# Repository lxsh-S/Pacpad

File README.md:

# Pacpad

*Pacpad* is a 4-key macropad with a rotatory encoder, an OLED screen and 2LEDs !!!!!!

I've used the KMK firmware for this macropad as python is way more easier than C.

## firmware fucntions

- Media control(prev track, play/pause, next track) with the SW2, SW3, and SW4 keys respectively
- Volume control with the rotatory encoder(volume up, volume down and mute)
- The SW1 key is binded with the F11 key for fullscreen

## PCB

This is my first ever PCB that I made in Kicad. I changed the design like 4 times lol T_T

PCB:

Schematic:

3D:

## CAD

This case was made in fusion360(I dualbooted win11 for that :))

- Top:

- Bottom: `Note` -> `The hole at the bottom of this design is for a screw that I already have with me (It is to hold the PCB at one place)`

- Knob: `Used the same as orpheuspad pad`

- Assembled:

## BOM

- 4x MX-Style switches
- 4x Black DSA Keys  
- 1x EC11 Rotatory encoder
- 1x 0.91 inch OLED display
- 2x SK6812MINI-E LEDs
- 1x Seed Xiao RP2040
- PCB made from the gerbers in the repo
- The top, bottom cases with the volume knob to be 3d printed from the `Production` folder

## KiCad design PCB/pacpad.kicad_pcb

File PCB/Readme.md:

# PCB

This pcb and the schematics were made in Kicad(it was my first time using it!)

## Design

- I first went through the default design that the hackpad kit's tutorial shows us
- Then I built on top of it and added another key, LEDs, OLED display and also a rotatory encoder
- I had to reroute the pcb way too many times cuz I was bring in major changes with each design change
- I didnt use matrix for the keys because we are only using 4 keys and ill be using up 4 GPIO pins anyway in the matrix

## Mistakes and Learnings

- The footprints and symbols are the most important thing for designing pcbs!! - I forgot this way too many times :(
- Learnt to use Kicad and also how footprints work and how really does a pcb work, it;s just a normal connection that we can build with a breadboard (but way more harder). Custom printed boards are used so that we can minimize the mess that we'll create traditionally!

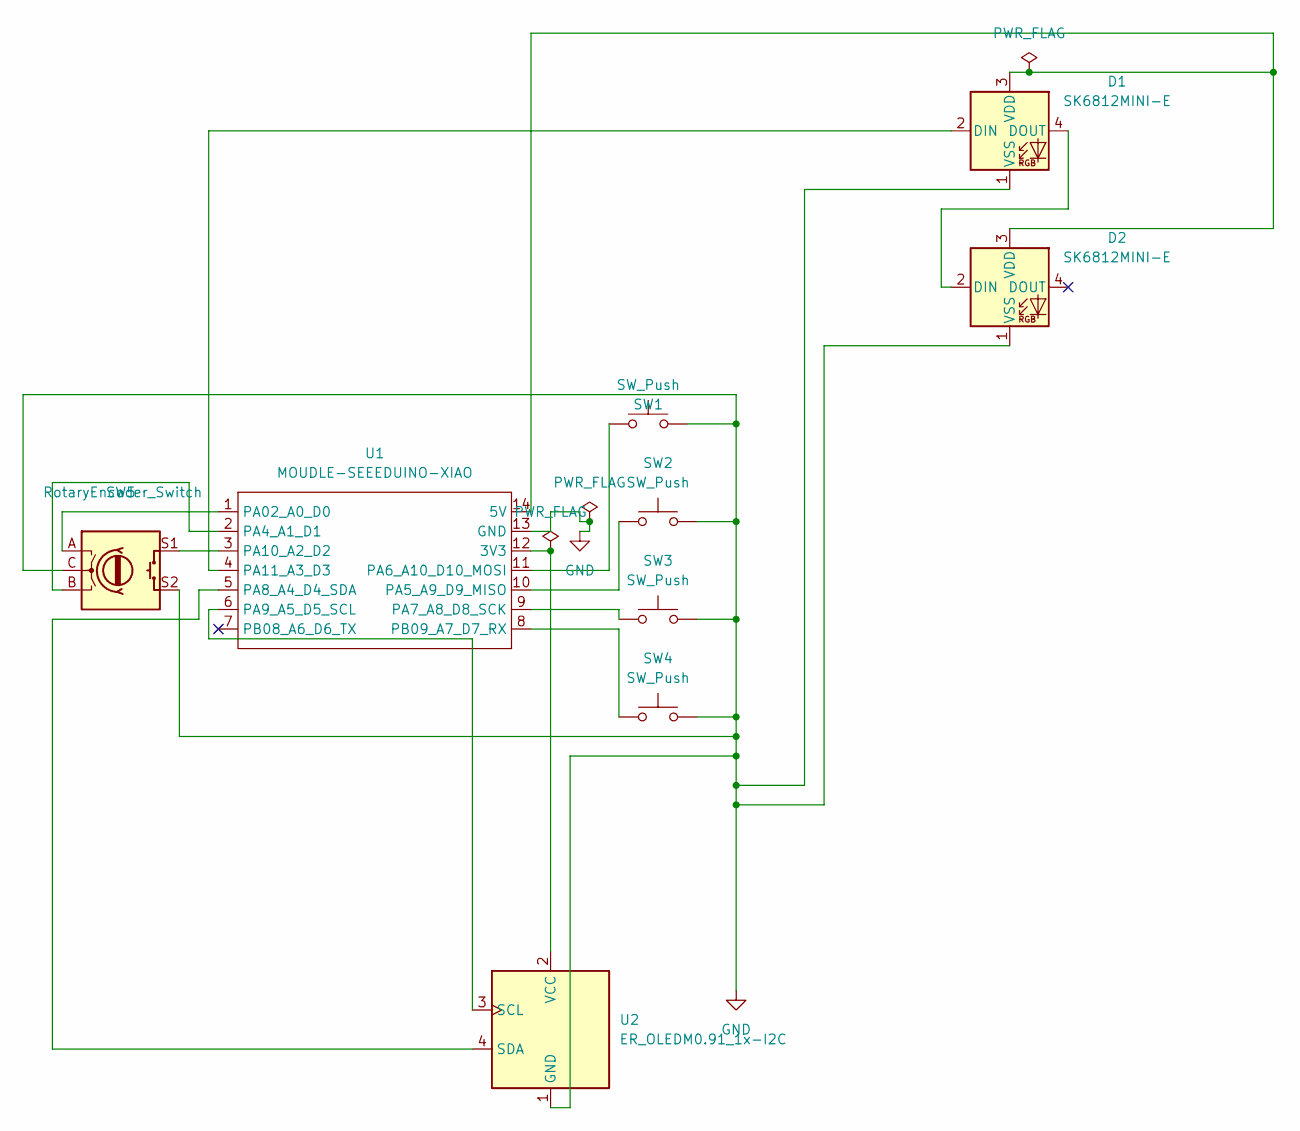
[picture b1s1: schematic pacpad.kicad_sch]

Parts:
D1, D2: SK6812MINI-E; SK6812MINI-E_fixed
SW1, SW2, SW3, SW4: SW_Push; SW_Cherry_MX_1.00u_PCB
SW5: RotaryEncoder_Switch; RotaryEncoder_Alps_EC11E-Switch_Vertical_H20mm_CircularMoun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
U1: MOUDLE-SEEEDUINO-XIAO; XIAO-Generic-Hybrid-14P-2.54-21X17.8MM
U2: ER_OLEDM0.91_1x-I2C

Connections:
GND: D1.1 (VSS), D2.1 (VSS), SW1.2, SW2.2, SW3.2, SW4.2, SW5.C, SW5.S2, U1.13 (GND), U2.1 (GND)
unnamed: D1.2 (DIN), U1.4 (PA11_A3_D3)
unnamed: D1.4 (DOUT), D2.2 (DIN)
unnamed: D1.3 (VDD), D2.3 (VDD), U1.14 (5V)
unnamed: U1.12 (3V3), U2.2 (VCC)
unnamed: SW5.A, U1.1 (PA02_A0_D0)
unnamed: SW5.B, U1.2 (PA4_A1_D1)
unnamed: SW2.1, U1.10 (PA5_A9_D9_MISO)
unnamed: SW1.1, U1.11 (PA6_A10_D10_MOSI)
unnamed: SW3.1, U1.9 (PA7_A8_D8_SCK)
unnamed: U1.5 (PA8_A4_D4_SDA), U2.4 (SDA)
unnamed: U1.6 (PA9_A5_D5_SCL), U2.3 (SCL)
unnamed: SW5.S1, U1.3 (PA10_A2_D2)
unnamed: SW4.1, U1.8 (PB09_A7_D7_RX)

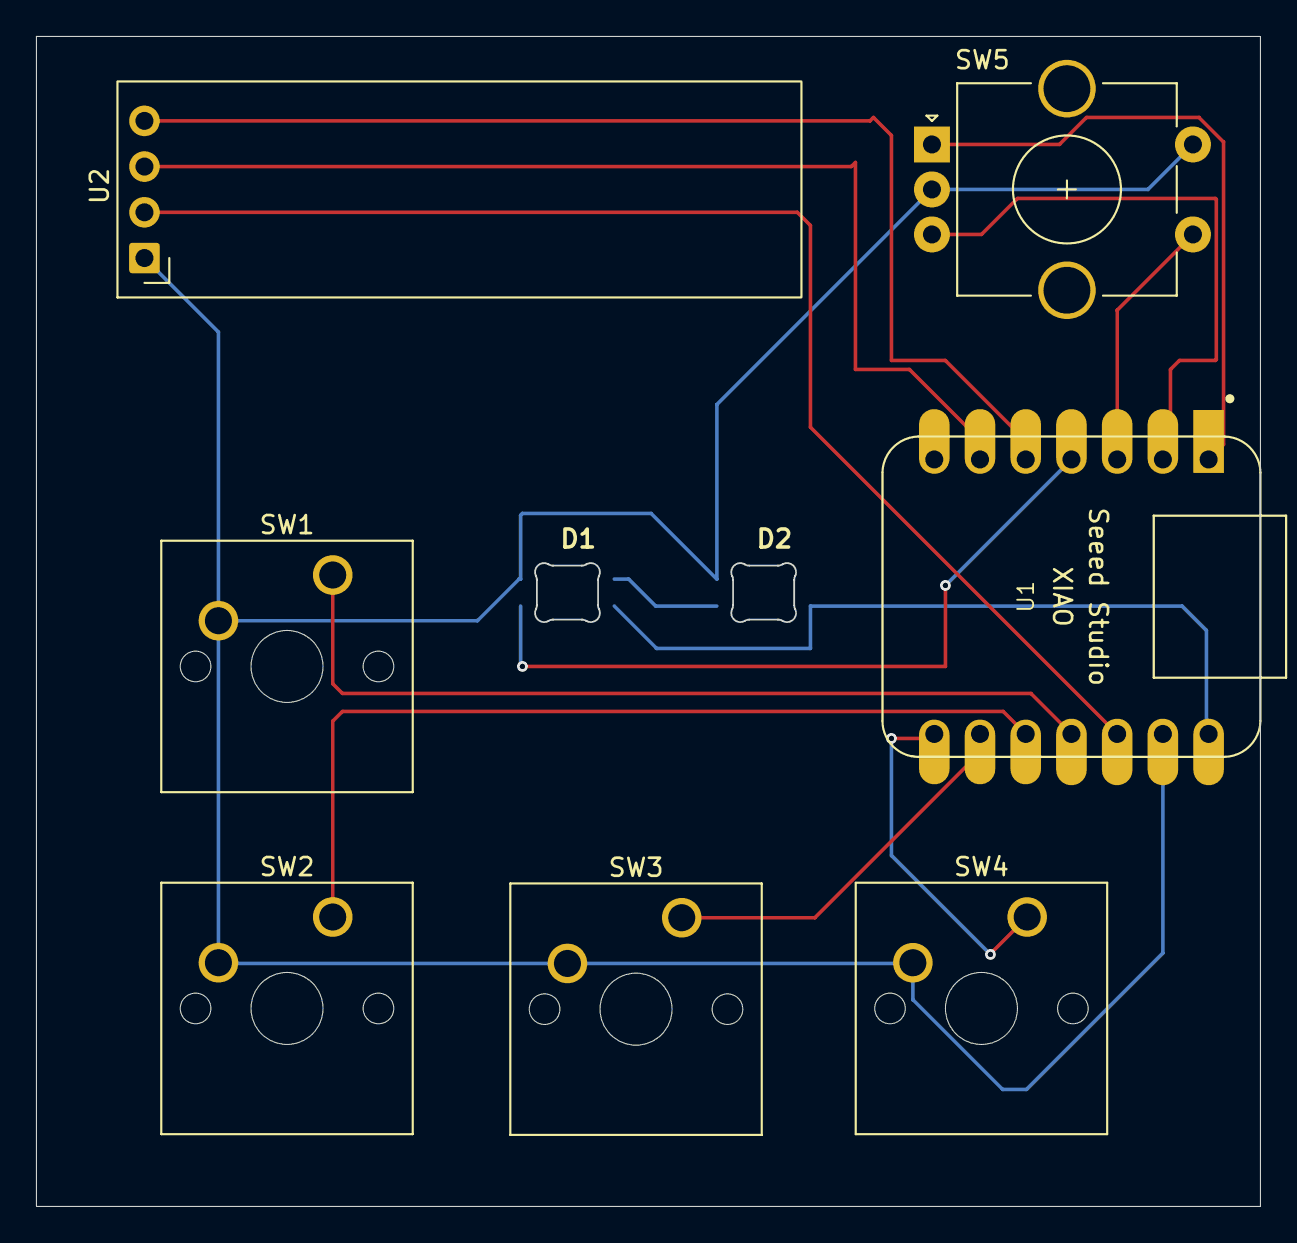
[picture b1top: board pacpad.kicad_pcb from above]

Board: 2 copper layers, 68.0 x 65.0 mm, 9 parts (0 on the bottom side), 14 nets.
